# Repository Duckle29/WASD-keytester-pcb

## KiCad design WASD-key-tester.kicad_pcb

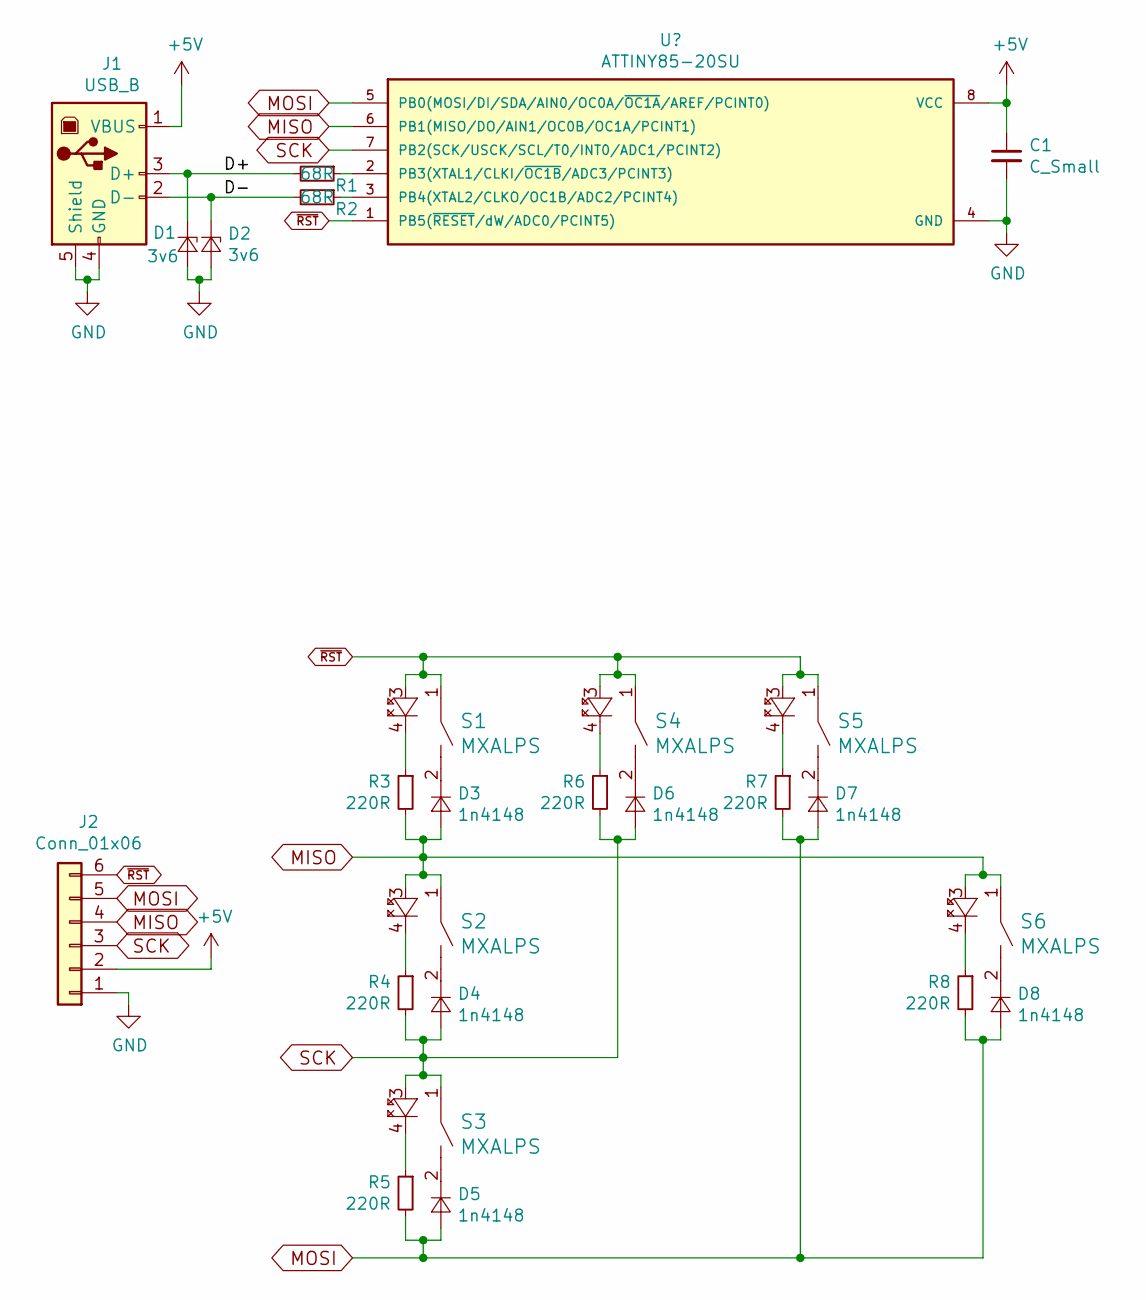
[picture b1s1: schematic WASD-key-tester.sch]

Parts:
C1: C_Small; C_0805_HandSoldering
D1, D2: 3v6; D_MiniMELF
D3, D4, D5, D6, D7, D8: 1n4148; D_SOD-123
J1: USB_B; USB_Micro_B
J2: Conn_01x06; Pin_Header_Straight_1x06_Pitch2.54mm
R1, R2: 68R; R_0603
R3, R4, R5, R6, R7, R8: 220R; R_0603
S1, S2, S3, S4, S5, S6: MXALPS; Cherry-MX-RGB-LED

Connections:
+5V: C1.1, J1.1 (VBUS), J2.2; also elsewhere on the board
/D+: D1.1 (K), J1.3 (D+), R1.2
/D-: D2.1 (K), J1.2 (D-), R2.2
GND: C1.2, D1.2 (A), D2.2 (A), J1.4 (GND), J1.5 (Shield), J2.1; also elsewhere on the board
MISO: D3.2 (A), J2.4, R3.2, S2.1, S2.3, S6.1, S6.3; also elsewhere on the board
MOSI: D5.2 (A), D7.2 (A), D8.2 (A), J2.5, R5.2, R7.2, R8.2; also elsewhere on the board
unnamed: D3.1 (K), S1.2
unnamed: D4.1 (K), S2.2
unnamed: D5.1 (K), S3.2
unnamed: D6.1 (K), S4.2
unnamed: D7.1 (K), S5.2
unnamed: D8.1 (K), S6.2
unnamed 12: R1.1; also elsewhere on the board
unnamed 13: R2.1; also elsewhere on the board
unnamed: R3.1, S1.4
unnamed: R4.1, S2.4
unnamed: R5.1, S3.4
unnamed: R6.1, S4.4
unnamed: R7.1, S5.4
unnamed: R8.1, S6.4
SCK: D4.2 (A), D6.2 (A), J2.3, R4.2, R6.2, S3.1, S3.3; also elsewhere on the board
~RST: J2.6, S1.1, S1.3, S4.1, S4.3, S5.1, S5.3; also elsewhere on the board

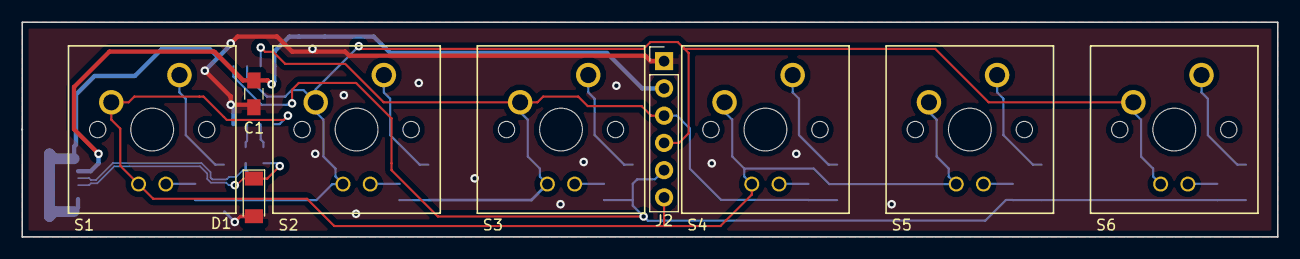
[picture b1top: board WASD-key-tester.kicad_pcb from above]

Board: 2 copper layers, 117.0 x 20.0 mm, 26 parts (0 on the bottom side), 22 nets.

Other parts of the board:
U1: ATTINY85-20SU; SOIC-8_3.9x4.9mm_Pitch1.27mm

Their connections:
+5V: U1.8; also elsewhere on the board
GND: U1.4; also elsewhere on the board
MISO: U1.6; also elsewhere on the board
MOSI: U1.5; also elsewhere on the board
unnamed 12: U1.2; also elsewhere on the board
unnamed 13: U1.3; also elsewhere on the board
SCK: U1.7; also elsewhere on the board
~RST: U1.1; also elsewhere on the board

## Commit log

2017-10-19 Added renders to readme
2017-10-19 Fixed links
2017-10-20 First writeup of the firmware. Not yet compiled
2017-10-20 Changed a bit of code on a tip from timemage :)
2017-10-20 made power traces bigger beceause why not
2018-02-10 Fixed firmware a bit
